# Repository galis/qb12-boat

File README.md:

# Boat QB12 · 手柄遥控的 3D 打印双体船

[English](README_en.md)

一艘从零做起的遥控双体船：自己画的主控板（嘉立创 SMT 贴片）、程序化生成的 3D 打印船体、ESP32-S3 固件，用 Xbox 手柄（蓝牙）或手机网页（Wi‑Fi）遥控。
配套两门网页课，讲清楚这块板子上每个电路为什么这样设计、PCB 怎么一步步画出来。

整个项目是和 AI 编程助手（Claude Code）一起做的，协作用的规则文件也放在仓库里，见下面的「和 AI 一起做」。

## 里面有什么

| 部分 | 内容 | 位置 |
|---|---|---|
| 主控板 | ESP32-S3-WROOM-1 + DRV8833 双路电机驱动 + TP4056 锂电充电 + AP2112K 3.3 V 稳压，USB-C，2 层板 56 × 38 mm | `hardware/pcb/` |
| 船体 | 双体船身、甲板（船头插舌 + 船尾旋钮扣，免螺丝）、舱罩、旋钮，Python 脚本生成 | `hardware/hull/` |
| 装配检查 | 板子、电机、电池、尾轴和船体有没有干涉，逐项算体积重叠 | `hardware/fitcheck/` |
| 固件 | Arduino + Bluepad32：Xbox 手柄模式、手机热点网页模式、低电压保护、插 USB 时禁用电机 | `firmware/` |
| 3D 预览 | three.js 预览页、装配动画 | `viewer/` |
| 电路课 | 10 课，从 USB-C 供电讲到 H 桥和 PWM，都以这块板子为例 | `courses/circuit/` |
| PCB 课 | 9 课，从原理图、布局、布线讲到 DRC 和嘉立创下单 | `courses/pcb/` |
| 成品文件 | Gerber、BOM、坐标文件、STL、KiCad 工程包、课程网页 | `outputs/QB12/` |
| 文档 | 开发环境、踩过的坑、设计评审、开放问题 | `docs/` |

## 直接用成品

**在线看课和 3D 预览：https://galis.github.io/qb12-boat/**

- **看课**：上面的网址，或者下载后用浏览器打开 `outputs/QB12/QB12_电路课.html`、`outputs/QB12/QB12_PCB课.html`，单文件，不用联网。
- **做板子**：嘉立创下单用 `outputs/QB12/` 里的 `QB12_Gerber.zip`、`QB12_BOM_嘉立创SMT.csv`、`QB12_CPL_坐标文件.csv`。ESP32 模组要选标准型 SMT（经济型不贴）。
- **打印船体、买材料**：`QB12_hull.stl`、`QB12_deck.stl`、`QB12_canopy.stl`、`QB12_knob.stl`（旋钮打 2 个），光敏树脂打印。打印要求、材料清单（电机、尾轴、电池等，附搜索词）和工具见网站上的 [打印和材料](https://galis.github.io/qb12-boat/build.html)，源文件是 `build.html`。
- **烧固件**：见 `firmware/README.md`。

## 从源文件重新生成

环境（macOS 上做的，Linux 大体一样）：Python 3.12、KiCad 10、arduino-cli、Java 21（Freerouting 用）。详细步骤见 `docs/开发环境.md`。

```bash
python3 -m venv .venv && source .venv/bin/activate && pip install -r requirements.txt

# 船体 → STL / USDZ，再做装配检查
cd hardware/hull && python build_model.py out && python export_assembly.py out && cd ../..
python hardware/fitcheck/check_pcb_fit.py

# 固件
firmware/build.sh

# PCB 课页面 + 测试
cd courses/pcb && python build.py --strict && python tools/test.py
```

自动布线用的 Freerouting 1.9.0 没有放进仓库，要从 [官方发布页](https://github.com/freerouting/freerouting/releases/tag/v1.9.0) 下载，放到 `tools/freerouting-1.9.0.jar`。

## 现状和已知问题（Rev A）

- 板子已打样、上电，桌面测试全部通过：充电、电池电压检测、手柄连接、两个电机正反转。
- 第一次下水能跑，但蓝牙不到 10 m 就断了。推测原因：PCB 天线离水面只有约 1.3 cm，Xbox 手柄的发射功率又小。固件已加手机 Wi‑Fi 模式，还没实测距离。Rev B 打算换外接天线的模组（ESP32-S3-WROOM-1U），把天线竖高。
- 其他评审意见见 `docs/QB12_RevA_评审.md`，没解决的问题见 `docs/开放问题.md`。

## 和 AI 一起做

- `CLAUDE.md`：每次对话都会带上的项目规则（目录、常用命令、禁区、怎么派子任务、怎么汇报）。
- `PLAN.template.md`：长任务的进度记录模板。AI 的对话上下文会被压缩，进度和决定要写进文件，下次接着做。
- `docs/坑.md`：踩过的坑，按领域分组，写成「现象 → 原因/做法」。
- `courses/pcb/AUTHORS.md`：PCB 课是分课交给多个 AI 子任务并行写的，这是给它们的统一说明。

## 许可证

- 硬件设计（`hardware/`、`outputs/QB12/` 里的制造文件）：CERN-OHL-P-2.0
- 代码（`firmware/`、`viewer/`、`tools/` 和各处的构建脚本）：MIT
- 文档和课程（`docs/`、`courses/` 的课文）：CC BY 4.0

详见 [LICENSE](LICENSE)。元件 3D 模型等第三方内容见 [NOTICE.md](NOTICE.md)。

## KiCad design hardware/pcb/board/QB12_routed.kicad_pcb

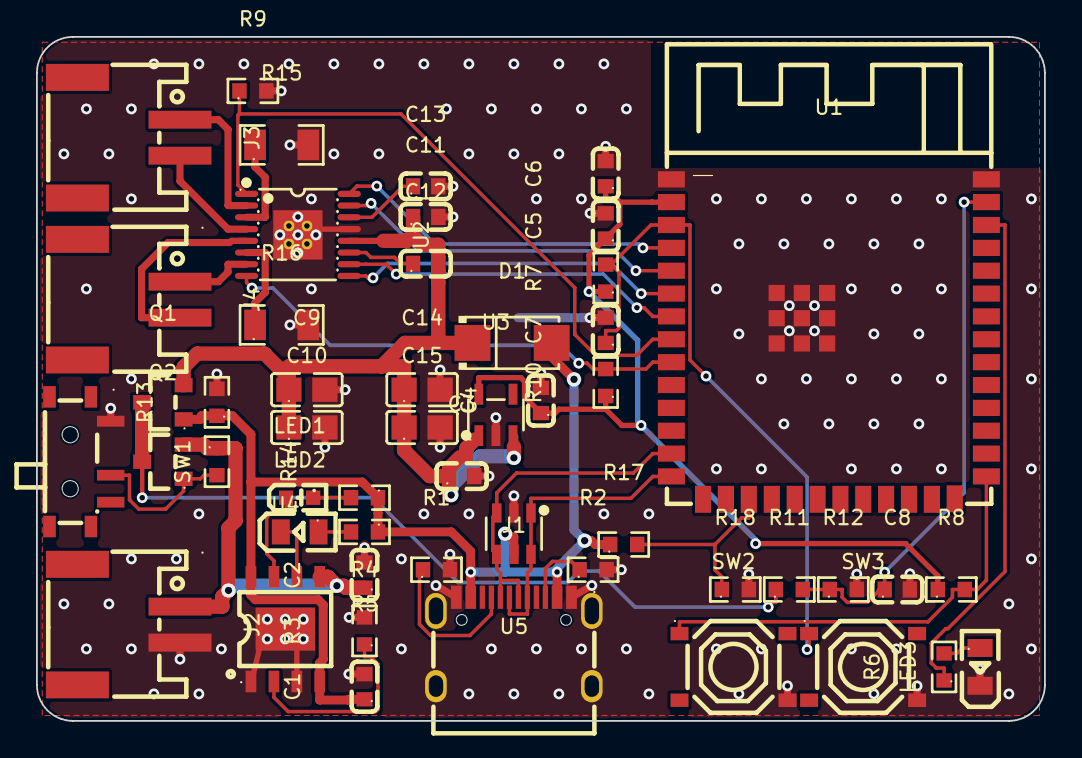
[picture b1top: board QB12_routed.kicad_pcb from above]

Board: 2 copper layers, 56.0 x 38.0 mm, 51 parts (0 on the bottom side), 36 nets.

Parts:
C1, C2, C4, C5: 10µF; C0603
C3, C7: 1µF; C0603
C6, C8, C11: 100nF; C0603
C9, C10, C14, C15: 22µF; C0805
C12: 10nF; C0603
C13: 2.2µF; C0603
D1: SS34; SMA_L4.3-W2.6-LS5.2-RD
J1: TYPE-C-31-M-12; USB-C_SMD-TYPE-C-31-M-12_1
J2, J3, J4: WAFER-PH2.0-2PWB; CONN-SMD_2P-P2.00_XUNPU_WAFER-PH2.0-2PWB
LED1: 红 0603; LED-SMD_L1.6-W0.8-R-RD
LED2, LED3: 绿 0805; LED0805-R-RD
Q1, Q2: AO3401A; SOT-23_L2.9-W1.3-P1.90-LS2.4-BR
R1, R2: 5.1kΩ; R0603
R3: 2kΩ; R0603
R4, R5, R6: 1kΩ; R0603
R7, R8, R9, R10, R13: 10kΩ; R0603
R11, R12, R14, R17, R18: 100kΩ; R0603
R15, R16: 0.2Ω 1206; R1206
SW1: MSK12C02; SW-TH_MSK12C02
SW2, SW3: TS-1187A-B-A-B; SW-SMD_4P-L5.1-W5.1-P3.70-LS6.5-TL_H1.5
U1: ESP32-S3-WROOM-1-N8R2; WIRELM-SMD_ESP32-S3-WROOM-1
U2: DRV8833PWPR; TSSOP-16_L5.0-W4.4-P0.65-LS6.4-BL-EP
U3: ME6211C33M5G-N; SOT-23-5_L3.0-W1.7-P0.95-LS2.8-BL
U4: TP4056-42-ESOP8; ESOP-8_L4.9-W3.9-P1.27-LS6.0-BL-EP
U5: USBLC6-2SC6; SOT-23-6_L2.9-W1.6-P0.95-LS2.8-BL

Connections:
3V3: C4.1, C5.1, C6.1, R7.1, R8.1, R10.1, U1.2, U3.5
AIN1: U1.4, U2.16
AIN2: U1.5, U2.15
BAT+: C2.1, J2.1, Q2.2, R14.1, U4.5
BAT_SW: Q1.3, Q2.3, R11.1
BIN1: U1.6, U2.9
BIN2: U1.7, U2.10
BOOT: R8.2, SW2.1, U1.27
CC1: J1.A5, R1.1
CC2: J1.B5, R2.1
CHRG: LED1.2, U4.7
EN: C7.1, R7.2, SW3.1, U1.3
GND: C1.2, C2.2, C3.2, C4.2, C5.2, C6.2, C7.2, C8.2, C9.2, C10.2, C11.2, C13.2, C14.2, C15.2, J1.1, J1.2, J1.3, J1.4, J1.A1B12, J1.B1A12, J2.2, LED3.2, R1.2, R2.2, R3.2, R9.2, R12.2, R13.2, R15.2, R16.2, R18.2, SW1.1, SW2.4, SW3.4, U1.1, U1.40, U1.41, U2.13, U2.17, U3.2, U4.1, U4.3, U4.9, U5.2
ISENA: R15.1, U2.3
ISENB: R16.1, U2.6
LED1_A: LED1.1, R4.2
LED2_A: LED2.1, R5.2
LED3_A: LED3.1, R6.2
LED_STAT: R6.1, U1.38
ML+: J3.1, U2.2
ML-: J3.2, U2.4
MR+: J4.1, U2.7
MR-: J4.2, U2.5
PROG: R3.1, U4.2
PWR_EN_N: Q2.1, R14.2, SW1.2
STDBY: LED2.2, U4.6
USB_DET: R17.2, R18.1, U1.17
USB_DN: J1.A7, J1.B7, U1.13, U5.3, U5.4
USB_DP: J1.A6, J1.B6, U1.14, U5.1, U5.6
VBAT_ADC: C8.1, R11.2, R12.1, U1.39
VBUS: C1.1, D1.2, J1.A4B9, J1.B4A9, Q1.1, R4.1, R5.1, R13.1, R17.1, U4.4, U4.8, U5.5
VCP: C12.1, U2.11
VINT: C13.1, U2.14
VSYS: C3.1, C9.1, C10.1, C11.1, C12.2, C14.1, C15.1, D1.1, Q1.2, U2.12, U3.1, U3.3
nFAULT: R10.2, U1.9, U2.8
nSLEEP: R9.1, U1.8, U2.1

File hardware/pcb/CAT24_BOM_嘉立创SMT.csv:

Comment,Designator,Footprint,Quantity,LCSC Part #
ESP32-S3-WROOM-1-N8R2,U1,ESP32-S3-WROOM-1,1,C2913204
DRV8833PWPR,U2,HTSSOP-16-EP,1,C50506
ME6211C33M5G-N,U3,SOT-23-5,1,C82942
TP4056-42-ESOP8,U4,ESOP-8,1,C16581
USBLC6-2SC6,U5,SOT-23-6,1,C7519
AO3401A,"Q1,Q2",SOT-23,2,C15127
SS34,D1,SMA,1,C8678
红 0603,LED1,LED-0603,1,C2286
绿 0805,"LED2,LED3",LED-0805,2,C2297
TYPE-C-31-M-12,J1,USB-C-SMD-16P,1,C165948
WAFER-PH2.0-2PWB,"J2,J3,J4",PH2.0-2P-SMD-H,3,C3029440
MSK12C02,SW1,SW-SMD-MSK12C02,1,C431540
TS-1187A-B-A-B,"SW2,SW3",SW-SMD-5.1x5.1,2,C318884
5.1kΩ,"R1,R2",0603,2,C23186
2kΩ,R3,0603,1,C22975
1kΩ,"R4,R5,R6",0603,3,C21190
10kΩ,"R7,R8,R9,R10,R13",0603,5,C25804
100kΩ,"R11,R12,R14,R17,R18",0603,5,C25803
0.2Ω 1206,"R15,R16",1206,2,C25335
10µF,"C1,C2,C4,C5",0603,4,C19702
1µF,"C3,C7",0603,2,C15849
100nF,"C6,C8,C11",0603,3,C14663
22µF,"C9,C10,C14,C15",0805,4,C45783
10nF,C12,0603,1,C57112
2.2µF,C13,0603,1,C23630

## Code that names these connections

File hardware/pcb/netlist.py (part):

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    "SW3": dict(value="TS-1187A-B-A-B", lcsc="C318884", fp="SW-SMD-5.1x5.1", lib="基础", kind="sw", desc="RESET 按键",
                pins=("EN", "GND")),
    # ---------- 二极管 / LED ----------
    "D1": dict(value="SS34", lcsc="C8678", fp="SMA", lib="基础", kind="d", desc="USB 供电二极管", pins=("VBUS", "VSYS")),
    "LED1": dict(value="红 0603", lcsc="C2286", fp="LED-0603", lib="基础", kind="led", desc="充电中", pins=("LED1_A", "CHRG")),
    "LED2": dict(value="绿 0805", lcsc="C2297", fp="LED-0805", lib="基础", kind="led", desc="充满", pins=("LED2_A", "STDBY")),
    "LED3": dict(value="绿 0805", lcsc="C2297", fp="LED-0805", lib="基础", kind="led", desc="状态灯", pins=("LED3_A", "GND")),
    # ---------- 电阻 ----------
    "R1": dict(value="5.1kΩ", lcsc="C23186", fp="0603", lib="基础", kind="r", desc="CC1 下拉", pins=("CC1", "GND")),
    "R2": dict(value="5.1kΩ", lcsc="C23186", fp="0603", lib="基础", kind="r", desc="CC2 下拉", pins=("CC2", "GND")),
    "R3": dict(value="2kΩ", lcsc="C22975", fp="0603", lib="基础", kind="r", desc="充电电流 ≈0.55A", pins=("PROG", "GND")),
    "R4": dict(value="1kΩ", lcsc="C21190", fp="0603", lib="基础", kind="r", desc="LED1 限流", pins=("VBUS", "LED1_A")),
    "R5": dict(value="1kΩ", lcsc="C21190", fp="0603", lib="基础", kind="r", desc="LED2 限流", pins=("VBUS", "LED2_A")),
    "R6": dict(value="1kΩ", lcsc="C21190", fp="0603", lib="基础", kind="r", desc="LED3 限流", pins=("LED_STAT", "LED3_A")),
    "R7": dict(value="10kΩ", lcsc="C25804", fp="0603", lib="基础", kind="r", desc="EN 上拉", pins=("3V3", "EN")),
    "R8": dict(value="10kΩ", lcsc="C25804", fp="0603", lib="基础", kind="r", desc="IO0 上拉", pins=("3V3", "BOOT")),
    "R9": dict(value="10kΩ", lcsc="C25804", fp="0603", lib="基础", kind="r", desc="nSLEEP 下拉", pins=("nSLEEP", "GND")),
    "R10": dict(value="10kΩ", lcsc="C25804", fp="0603", lib="基础", kind="r", desc="nFAULT 上拉", pins=("3V3", "nFAULT")),
    "R11": dict(value="100kΩ", lcsc="C25803", fp="0603", lib="基础", kind="r", desc="电压检测分压", pins=("BAT_SW", "VBAT_ADC")),
    "R12": dict(value="100kΩ", lcsc="C25803", fp="0603", lib="基础", kind="r", desc="电压检测分压", pins=("VBAT_ADC", "GND")),
    "R13": dict(value="10kΩ", lcsc="C25804", fp="0603", lib="基础", kind="r", desc="Q1 栅极下拉", pins=("VBUS", "GND")),
    "R14": dict(value="100kΩ", lcsc="C25803", fp="0603", lib="基础", kind="r", desc="Q2 栅极上拉（关机）", pins=("BAT+", "PWR_EN_N")),
    "R15": dict(value="0.2Ω 1206", lcsc="C25335", fp="1206", lib="扩展", kind="r", desc="A 路限流 ≈1A", pins=("ISENA", "GND")),
    "R16": dict(value="0.2Ω 1206", lcsc="C25335", fp="1206", lib="扩展", kind="r", desc="B 路限流 ≈1A", pins=("ISENB", "GND")),
    "R17": dict(value="100kΩ", lcsc="C25803", fp="0603", lib="基础", kind="r", desc="USB 检测分压", pins=("VBUS", "USB_DET")),
    "R18": dict(value="100kΩ", lcsc="C25803", fp="0603", lib="基础", kind="r", desc="USB 检测分压", pins=("USB_DET", "GND")),
    # ---------- 电容 ----------
    "C1": dict(value="10µF", lcsc="C19702", fp="0603", lib="基础", kind="c", desc="TP4056 输入", pins=("VBUS", "GND")),
    "C2": dict(value="10µF", lcsc="C19702", fp="0603", lib="基础", kind="c", desc="电池端", pins=("BAT+", "GND")),
    "C3": dict(value="1µF", lcsc="C15849", fp="0603", lib="基础", kind="c", desc="LDO 输入", pins=("VSYS", "GND")),
    "C4": dict(value="10µF", lcsc="C19702", fp="0603", lib="基础", kind="c", desc="LDO 输出", pins=("3V3", "GND")),
    "C5": dict(value="10µF", lcsc="C19702", fp="0603", lib="基础", kind="c", desc="模组电源", pins=("3V3", "GND")),
    "C6": dict(value="100nF", lcsc="C14663", fp="0603", lib="基础", kind="c", desc="模组电源", pins=("3V3", "GND")),
    "C7": dict(value="1µF", lcsc="C15849", fp="0603", lib="基础", kind="c", desc="EN 延时", pins=("EN", "GND")),
    "C8": dict(value="100nF", lcsc="C14663", fp="0603", lib="基础", kind="c", desc="ADC 滤波", pins=("VBAT_ADC", "GND")),
    "C9": dict(value="22µF", lcsc="C45783", fp="0805", lib="基础", kind="c", desc="电机电源储能", pins=("VSYS", "GND")),
    "C10": dict(value="22µF", lcsc="C45783", fp="0805", lib="基础", kind="c", desc="电机电源储能", pins=("VSYS", "GND")),
    "C14": dict(value="22µF", lcsc="C45783", fp="0805", lib="基础", kind="c", desc="电机电源储能", pins=("VSYS", "GND")),
    "C15": dict(value="22µF", lcsc="C45783", fp="0805", lib="基础", kind="c", desc="电机电源储能", pins=("VSYS", "GND")),
    "C11": dict(value="100nF", lcsc="C14663", fp="0603", lib="基础", kind="c", desc="VM 去耦", pins=("VSYS", "GND")),
    "C12": dict(value="10nF", lcsc="C57112", fp="0603", lib="基础", kind="c", desc="VCP 电荷泵", pins=("VCP", "VSYS")),
    "C13": dict(value="2.2µF", lcsc="C23630", fp="0603", lib="基础", kind="c", desc="VINT 去耦", pins=("VINT", "GND")),
}


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
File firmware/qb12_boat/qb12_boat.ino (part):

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#include "phone_page.h"

// ---- 引脚：和 hardware/pcb/netlist.py 一一对应 ----
const int AIN1 = 4, AIN2 = 5;      // 左电机 J3
const int BIN1 = 6, BIN2 = 7;      // 右电机 J4
const int NSLEEP = 15, NFAULT = 16;
const int VBAT = 1, LED = 2;
const int USB_DET = 9;
const int BOOT_BTN = 0;            // SW2，按下为低（R8 上拉）             // VBUS 经 R17/R18 各 100k 分压，插 USB 时约 2.5 V

// ---- 可调参数 ----
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
void setup() {
  // 通道 → 频率 20kHz、10 位；再把引脚挂到通道上
  const int pins[4] = {AIN1, AIN2, BIN1, BIN2};
  for (int ch = 0; ch < 4; ch++) { ledcSetup(ch, 20000, 10); ledcAttachPin(pins[ch], ch); }
  drive(CH_A1, CH_A2, 0); drive(CH_B1, CH_B2, 0);
  Serial.begin(115200);
  pinMode(NFAULT, INPUT);          // 外面有 R10 上拉
  pinMode(LED, OUTPUT);
  pinMode(NSLEEP, OUTPUT);
  digitalWrite(NSLEEP, HIGH);      // 唤醒 DRV8833（平时被 R9 拉低）
  vbatF = analogReadMilliVolts(VBAT) * 2 / 1000.0;
  pinMode(BOOT_BTN, INPUT_PULLUP);
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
